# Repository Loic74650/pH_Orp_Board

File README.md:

# pH_Orp_Board
## A 16 bits, two-channels, analog to digital convertion board with galavnic isolation to measure pH and Orp levels in pools and similar environments

This project is based on the original project from Roberto Buti: https://github.com/reef-pi/pH-Board.<br />
This modified version features a double input for simultaneous pH and Orp measurements on the same board, based on the ADS1115 IC.<br />
This board is an ideal companion to the PoolMaster project: https://github.com/Loic74650/PoolMaster.<br />
The 5Volts power supply to this board should be low noise and low drift (sorry no spec).<br /><br />
A alternative (and likely better) routing of the board was performed by @Gixy31 and is available here: https://github.com/Gixy31/ESP32-PoolMaster/tree/main/pH_Orp%20Board%20V2

<br />

Schematics <br /><br />

<br />

PCB front <br /><br />

<br />

PCB back <br /><br />

<br />

PoolMaster dashboard with pH_Orp_Board integrated<br /><br />

<br />

Basic sketch provided in this repository to test the PCB with this library: <br /><br />
https://lygte-info.dk/project/ADS1115Library%20UK.html<br /><br />

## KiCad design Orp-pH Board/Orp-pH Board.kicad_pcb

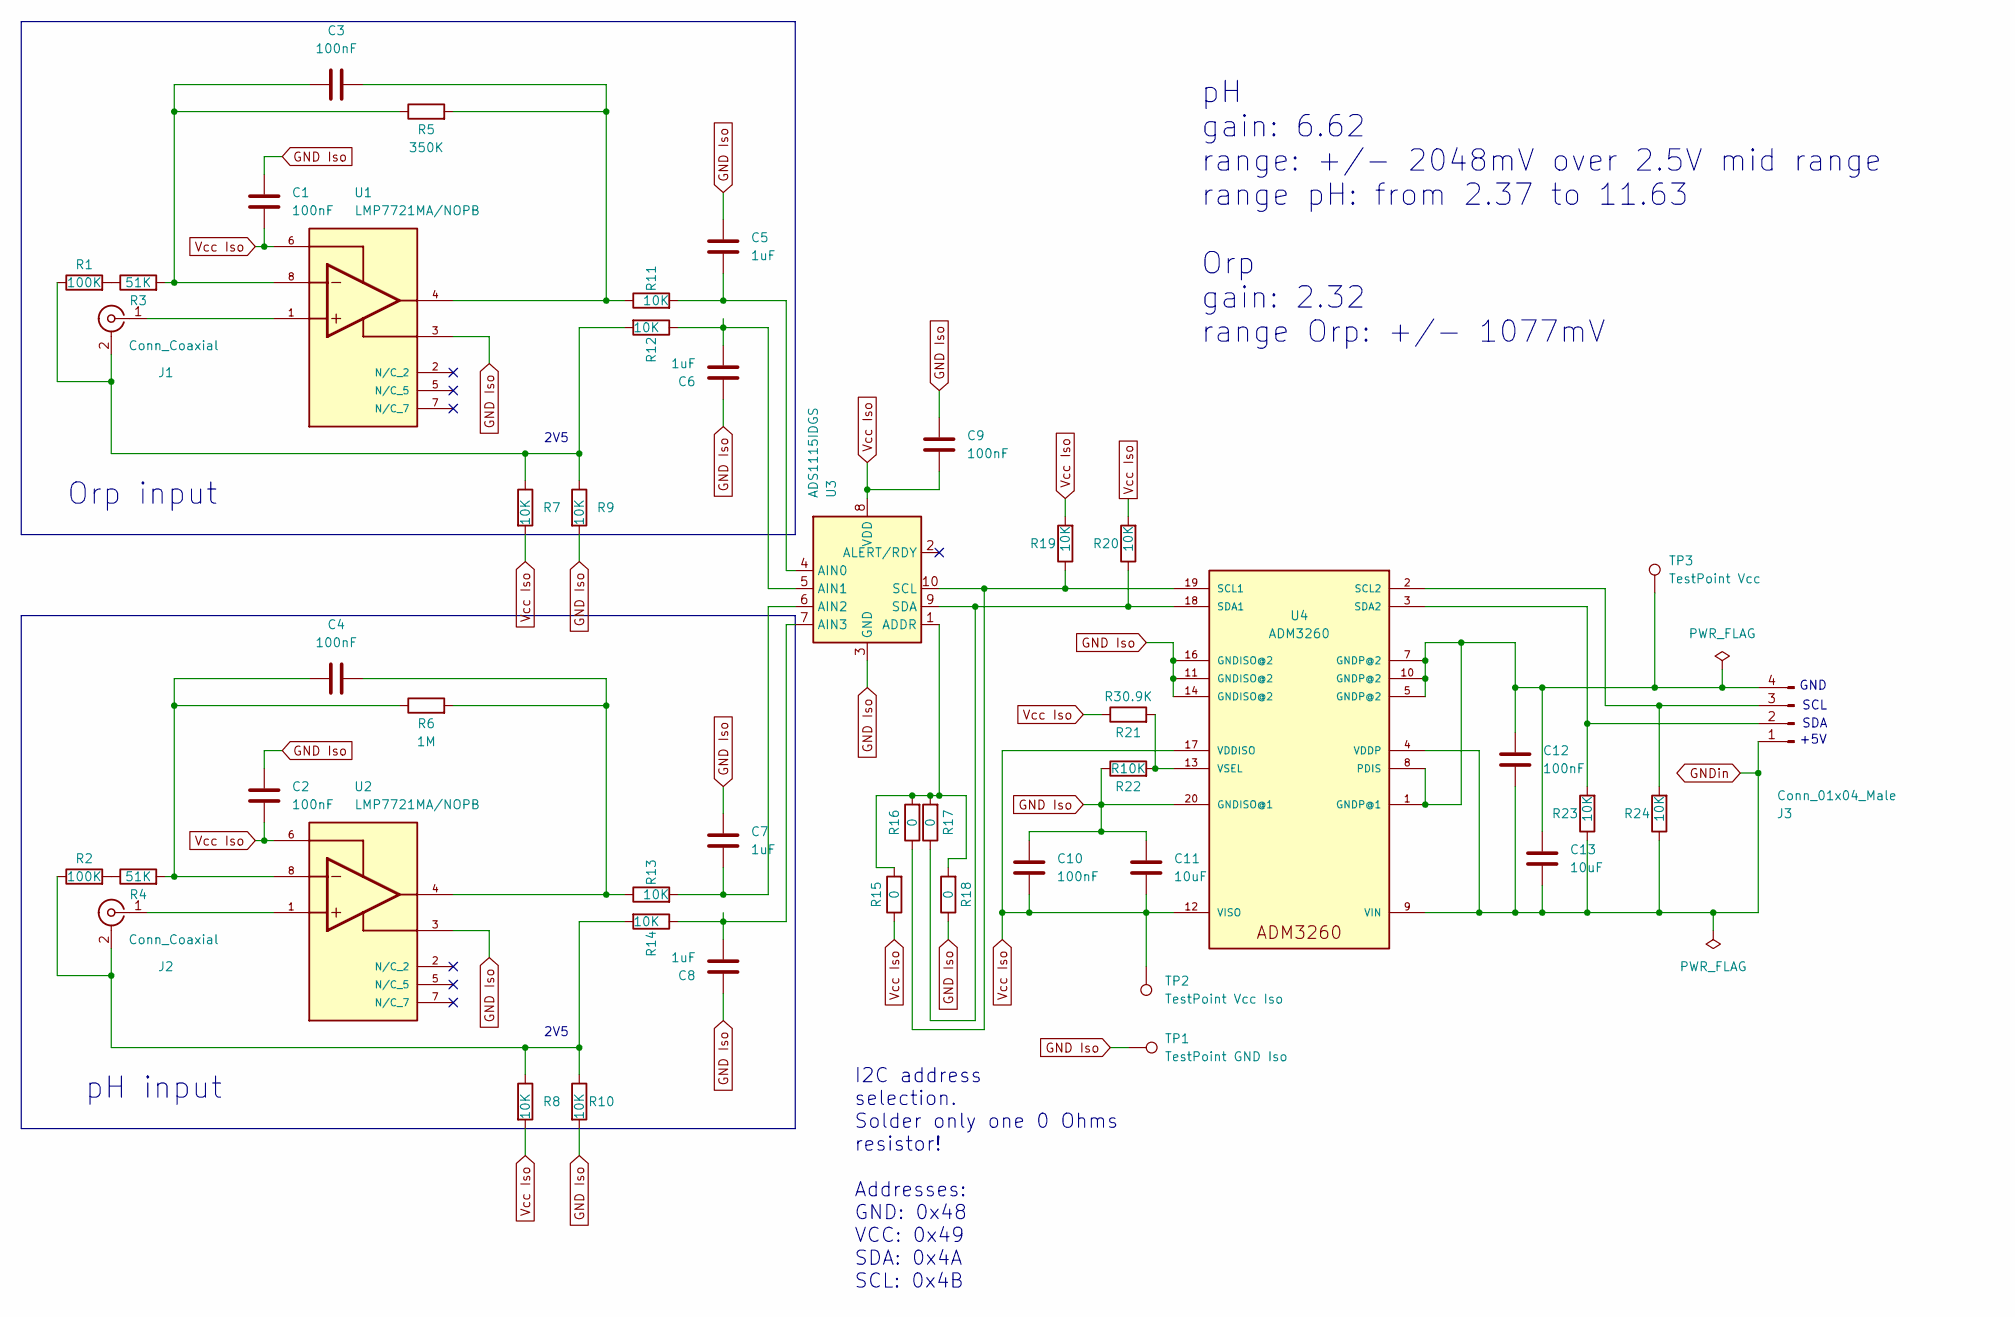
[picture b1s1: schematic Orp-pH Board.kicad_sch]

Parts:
C1, C2, C3, C4, C9, C10, C12: 100nF; C_0603_1608Metric_Pad1.08x0.95mm_HandSolder
C5, C6, C7, C8: 1uF; C_0603_1608Metric_Pad1.08x0.95mm_HandSolder
C11, C13: 10uF; C_1210_3225Metric_Pad1.33x2.70mm_HandSolder
J1, J2: Conn_Coaxial; BNC_Amphenol_B6252HB-NPP3G-50_Horizontal
J3: Conn_01x04_Male; PinHeader_1x04_P2.54mm_Vertical
R1, R2: 100K; C_0805_2012Metric_Pad1.18x1.45mm_HandSolder
R3, R4: 51K; C_0805_2012Metric_Pad1.18x1.45mm_HandSolder
R5: 350K; C_0805_2012Metric_Pad1.18x1.45mm_HandSolder
R6: 1M; C_0805_2012Metric_Pad1.18x1.45mm_HandSolder
R7, R8, R9, R10, R11, R12, R13, R14, R19, R20, R23, R24: 10K; C_0805_2012Metric_Pad1.18x1.45mm_HandSolder
R15, R16, R17, R18: 0; C_0805_2012Metric_Pad1.18x1.45mm_HandSolder
R21: R30.9K; C_0805_2012Metric_Pad1.18x1.45mm_HandSolder
R22: R10K; C_0805_2012Metric_Pad1.18x1.45mm_HandSolder
TP1: TestPoint GND Iso; TestPoint_Pad_D2.0mm
TP2: TestPoint Vcc Iso; TestPoint_Pad_D2.0mm
TP3: TestPoint Vcc; TestPoint_Pad_D2.0mm
U1, U2: LMP7721MA/NOPB; SOIC127P599X175-8N; PARTREV E
U3: ADS1115IDGS; VSSOP-10_3x3mm_P0.5mm
U4: ADM3260; SOP65P780X200-20N

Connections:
GND Iso: C1.1, C2.1, C5.1, C6.1, C7.1, C8.1, C9.1, C10.1, C11.1, R9.2, R10.2, R18.1, R22.1, TP1.1, U1.3, U2.3, U3.3 (GND), U4.11 (GNDISO@2), U4.14 (GNDISO@2), U4.16 (GNDISO@2), U4.20 (GNDISO@1)
unnamed: C3.1, R3.2, R5.1, U1.8
unnamed: C3.2, R5.2, R11.1, U1.4
unnamed: C4.1, R4.2, R6.1, U2.8
unnamed: C4.2, R6.2, R13.1, U2.4
unnamed: C5.2, R11.2, U3.4 (AIN0)
unnamed: C6.2, R12.1, U3.5 (AIN1)
unnamed: C7.2, R13.2, U3.6 (AIN2)
unnamed: C8.2, R14.1, U3.7 (AIN3)
unnamed: C12.2, C13.2, J3.1, R23.1, R24.1, U4.4 (VDDP), U4.9 (VIN)
unnamed: J1.1 (In), U1.1
unnamed: J1.2 (Ext), R1.1, R7.1, R9.1, R12.2
unnamed: J2.1 (In), U2.1
unnamed: J2.2 (Ext), R2.1, R8.1, R10.1, R14.2
unnamed: J3.2, R23.2, U4.3 (SDA2)
unnamed: J3.3, R24.2, U4.2 (SCL2)
unnamed: R1.2, R3.1
unnamed: R2.2, R4.1
unnamed: R15.2, R16.2, R17.2, R18.2, U3.1 (ADDR)
unnamed: R16.1, R19.1, U3.10 (SCL), U4.19 (SCL1)
unnamed: R17.1, R20.1, U3.9 (SDA), U4.18 (SDA1)
unnamed: R21.2, R22.2, U4.13 (VSEL)
Vcc Iso: C1.2, C2.2, C9.2, C10.2, C11.2, R7.2, R8.2, R15.1, R19.2, R20.2, R21.1, TP2.1, U1.6, U2.6, U3.8 (VDD), U4.12 (VISO), U4.17 (VDDISO)

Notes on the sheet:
+5V
GND
Orp input
SDA
I2C address selection. Solder only one 0 Ohms resistor! Addresses: GND: 0x48 VCC: 0x49 SDA: 0x4A SCL: 0x4B
SCL
2V5
pH input
pH gain: 6.62 range: +/- 2048mV over 2.5V mid range range pH: from 2.37 to 11.63 Orp gain: 2.32 range Orp: +/- 1077mV

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
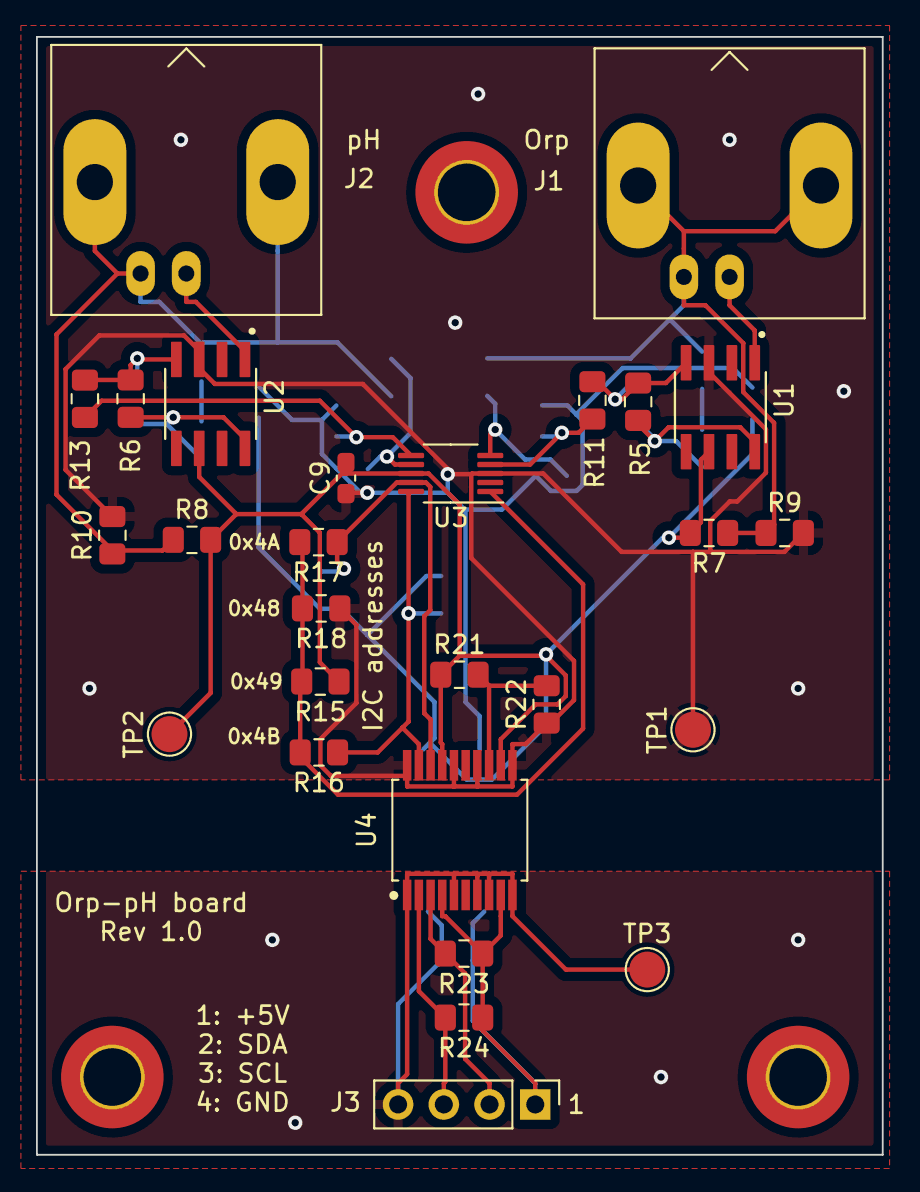
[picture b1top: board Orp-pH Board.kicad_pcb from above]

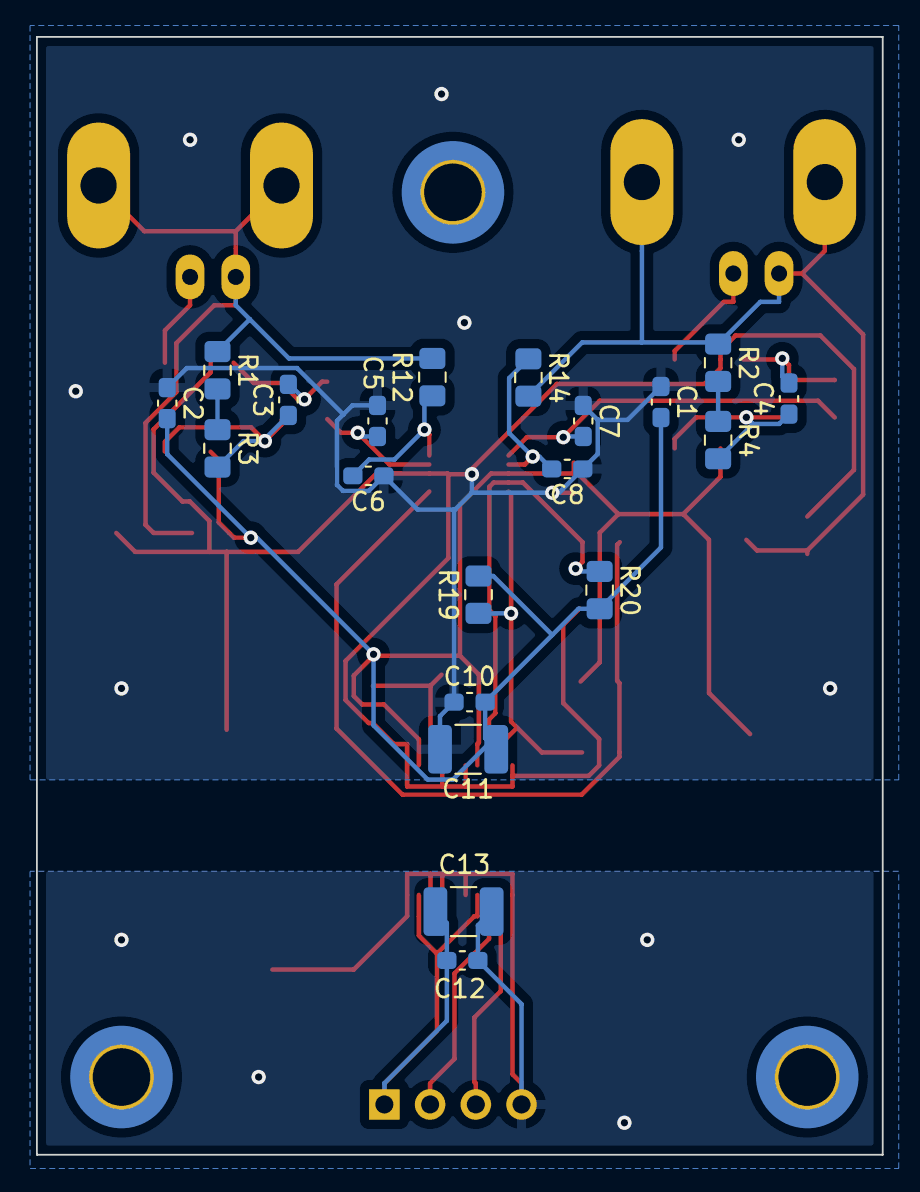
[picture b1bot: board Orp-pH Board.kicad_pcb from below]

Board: 2 copper layers, 47.0 x 62.1 mm, 50 parts (20 on the bottom side), 24 nets.

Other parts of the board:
REF1, REF2, REF3: MountingHole_3.2mm_M3_ISO7380_Pad_TopBottom

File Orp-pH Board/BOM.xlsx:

Column1 | Column2 | Column3 | Column4 | Column5 | Column6 | Column7 | Column8 | Column9
Source: | C:\Users\USER\Documents\GitHub\pH-Board\Kicad\Orp-pH Board\Orp-pH Board.kicad_s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
Date: | 25/05/2023 13:23:16
Tool: | Eeschema (6.0.11)
Generator: | C:\Program Files\KiCad\6.0\bin\scripting\plugins/bom_csv_grouped_by_value_with_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
Component Count: | 47
Ref | Qnty | Value | Cmp name | Footprint | Description | Vendor | Unit Price HT€ | Total Price HT€
C1, C2, C3, C4, C9, C10, C12, | 7 | 100nF | C | Capacitor_SMD:C_0603_1608Metric_Pad1.08x0.95mm_HandSolder | Unpolarized capacitor |  |  | 0
C5, C6, C7, C8, | 4 | 1uF | C | Capacitor_SMD:C_0603_1608Metric_Pad1.08x0.95mm_HandSolder | Unpolarized capacitor |  |  | 0
C11, C13, | 2 | 10uF | C | Capacitor_SMD:C_1210_3225Metric_Pad1.33x2.70mm_HandSolder | Unpolarized capacitor |  |  | 0
J1, J2, | 2 | Conn_Coaxial | Conn_Coaxial | Connector_Coaxial:BNC_Amphenol_B6252HB-NPP3G-50_Horizontal | coaxial connector (BNC, SMA, SMB, SMC, Cinch/RCA, LEMO, ...) | https://www.mouser.fr/ProductDetail/TE-Connectivity-AMP/2271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 | 6.06 | 12.12
J3, | 1 | Conn_01x04_Male | Conn_01x04_Male | Connector_PinHeader_2.54mm:PinHeader_1x04_P2.54mm_Vertical | Generic connector, single row, 01x04, script generated (kicad-library-utils/sch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 |  |  | 0
R1, R2, | 2 | 100K | R | Capacitor_SMD:C_0805_2012Metric_Pad1.18x1.45mm_HandSolder | Resistor |  |  | 0
R3, R4, | 2 | 51K | R | Capacitor_SMD:C_0805_2012Metric_Pad1.18x1.45mm_HandSolder | Resistor |  |  | 0
R5, | 1 | 350K | R | Capacitor_SMD:C_0805_2012Metric_Pad1.18x1.45mm_HandSolder | Resistor |  |  | 0
R6, | 1 | 1M | R | Capacitor_SMD:C_0805_2012Metric_Pad1.18x1.45mm_HandSolder | Resistor |  |  | 0
R7, R8, R9, R10, R11, R12, R13, R14, R19, R20, R23, R24, | 12 | 10K | R | Capacitor_SMD:C_0805_2012Metric_Pad1.18x1.45mm_HandSolder | Resistor |  |  | 0
R15, R16, R17, R18, | 4 | 0 | R | Capacitor_SMD:C_0805_2012Metric_Pad1.18x1.45mm_HandSolder | Resistor |  |  | 0
R21, | 1 | R30.9K | R | Capacitor_SMD:C_0805_2012Metric_Pad1.18x1.45mm_HandSolder | Resistor |  |  | 0
R22, | 1 | R10K | R | Capacitor_SMD:C_0805_2012Metric_Pad1.18x1.45mm_HandSolder | Resistor |  |  | 0
TP1, | 1 | TestPoint GND Iso | TestPoint | TestPoint:TestPoint_Pad_D2.0mm | test point |  |  | 0
TP2, | 1 | TestPoint Vcc Iso | TestPoint | TestPoint:TestPoint_Pad_D2.0mm | test point |  |  | 0
TP3, | 1 | TestPoint Vcc | TestPoint | TestPoint:TestPoint_Pad_D2.0mm | test point |  |  | 0
U1, U2, | 2 | LMP7721MA/NOPB | LMP7721MA{slash}NOPB | SOIC127P599X175-8N |  | https://www.ti.com/lit/ds/symlink/ads1115-q1.pdf?HQS=dis-mou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 | 5.68 | 11.36
U3, | 1 | ADS1115IDGS | ADS1115IDGS | Package_SO:TSSOP-10_3x3mm_P0.5mm | Ultra-Small, Low-Power, I2C-Compatible, 860-SPS, 16-Bit ADCs With Internal Refe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 |  | 6.26 | 6.26
U4, | 1 | ADM3260 | ADM3260 | ADM3260:SOP65P780X200-20N |  |  | 10.199999999999999 | 10.199999999999999
 |  |  |  |  |  |  | TOTAL HT€ | 39.94

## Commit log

2023-07-10 Cleaning up files
2023-07-10 added pics
2023-07-21 updated schema
2023-07-29 update value of R5 resistor
2023-08-25 fixed small errors on the schema
2023-09-18 fixed gain error in label of schematics
